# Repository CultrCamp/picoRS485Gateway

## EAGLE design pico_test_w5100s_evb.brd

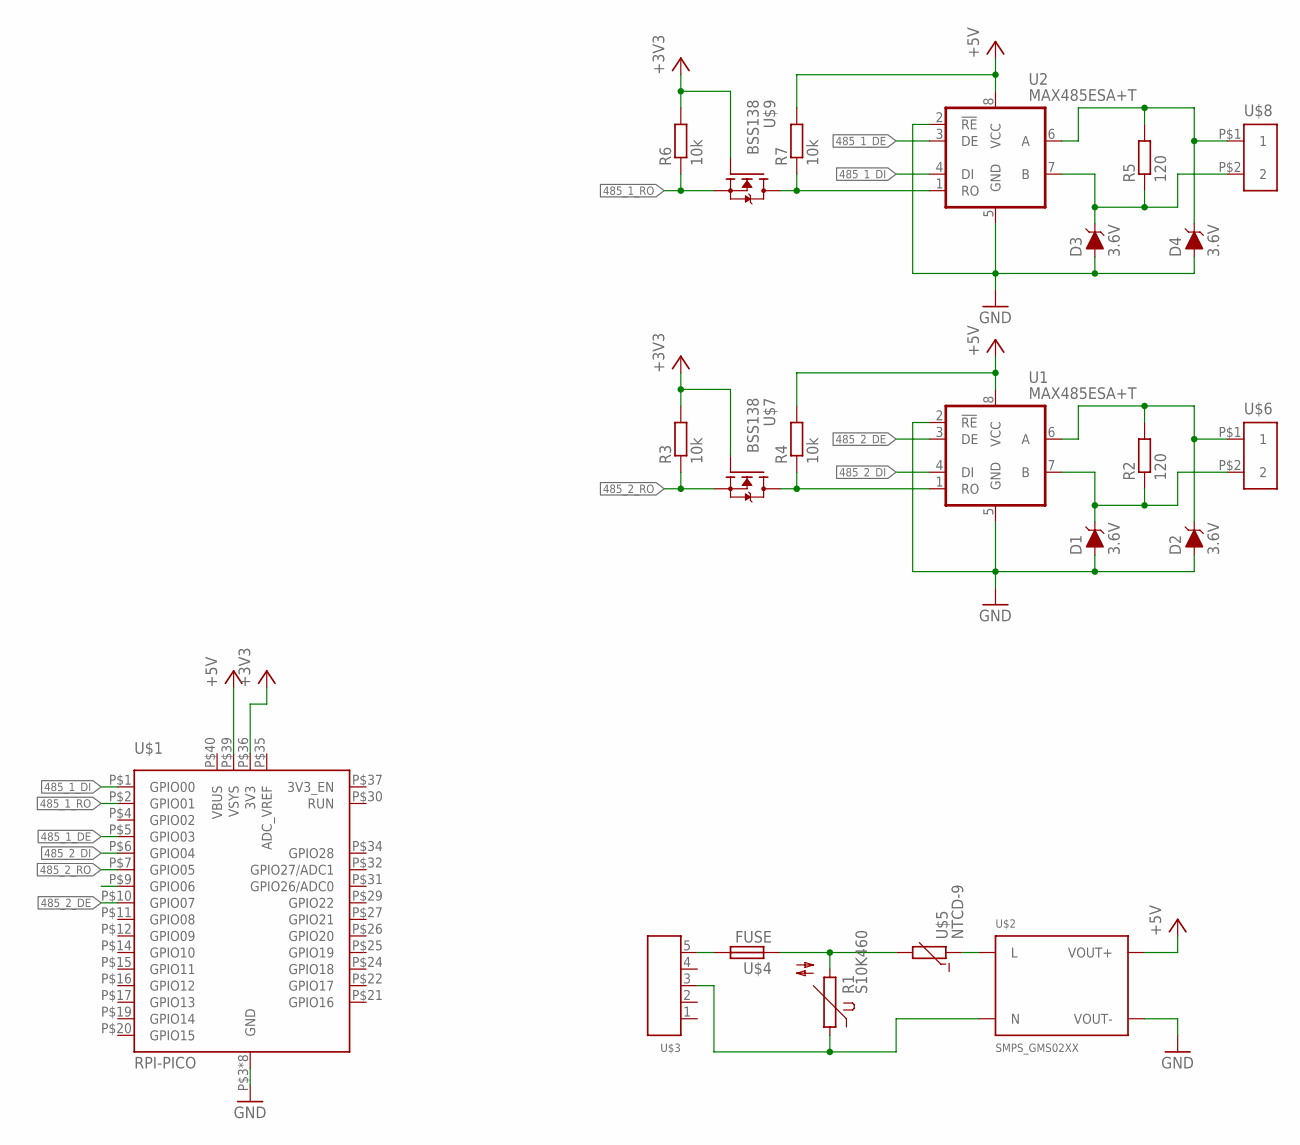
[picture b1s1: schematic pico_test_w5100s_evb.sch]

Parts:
D1, D2, D3, D4: 3.6V; SOD-323
R1: S10K460
R2, R5: 120; R0603
R3, R4, R6, R7: 10k; R0603
U1, U2: MAX485ESA+T; SOIC127P600X175-8N
U$1: RPI-PICO; W5100S-EVB-PICO
U$2: SMPS_GMS02XX; GMS02XX
U$3: XEHDR-5
U$4: FUSE; FUZEX8.5X4.5X5.08
U$5: NTCD-9; NTCXD-9
U$6, U$8: XEHDR-2; 5EHDR-2
U$7, U$9: BSS138; SOT95P240X110-3N

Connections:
485_1_DE: U2.3 (DE), U$1.P$5 (GPIO03)
485_1_DI: U2.4 (DI), U$1.P$1 (GPIO00)
485_1_RO: R6.1, U$1.P$2 (GPIO01), U$9.2 (S)
485_2_DE: U1.3 (DE), U$1.P$10 (GPIO07)
485_2_DI: U1.4 (DI), U$1.P$6 (GPIO04)
485_2_RO: R3.1, U$1.P$7 (GPIO05), U$7.2 (S)
+3V3: R3.2, R6.2, U$1.P$36 (3V3), U$7.1 (G), U$9.1 (G)
+5V: R4.2, R7.2, U1.8 (VCC), U2.8 (VCC), U$1.P$39 (VSYS), U$2.DC+ (VOUT+)
GND: D1.A, D2.A, D3.A, D4.A, U1.2 (!RE), U1.5 (GND), U2.2 (!RE), U2.5 (GND), U$1.P$3 (GND), U$1.P$8 (GND), U$1.P$13 (GND), U$1.P$18 (GND), U$1.P$23 (GND), U$1.P$28 (GND), U$1.P$33 (GND), U$1.P$38 (GND), U$2.DC- (VOUT-)
unnamed: U$3.5, U$4.P$2 (2)
unnamed: R1.2, U$4.P$1 (1), U$5.P$2 (2)
unnamed: U$2.P$1 (L), U$5.P$1 (1)
unnamed: R1.1, U$2.P$2 (N), U$3.3
unnamed: R4.1, U1.1 (RO), U$7.3 (D)
unnamed: D1.C, R2.1, U1.7 (B), U$6.P$2 (2)
unnamed: D2.C, R2.2, U1.6 (A), U$6.P$1 (1)
unnamed: D3.C, R5.1, U2.7 (B), U$8.P$2 (2)
unnamed: D4.C, R5.2, U2.6 (A), U$8.P$1 (1)
unnamed: R7.1, U2.1 (RO), U$9.3 (D)

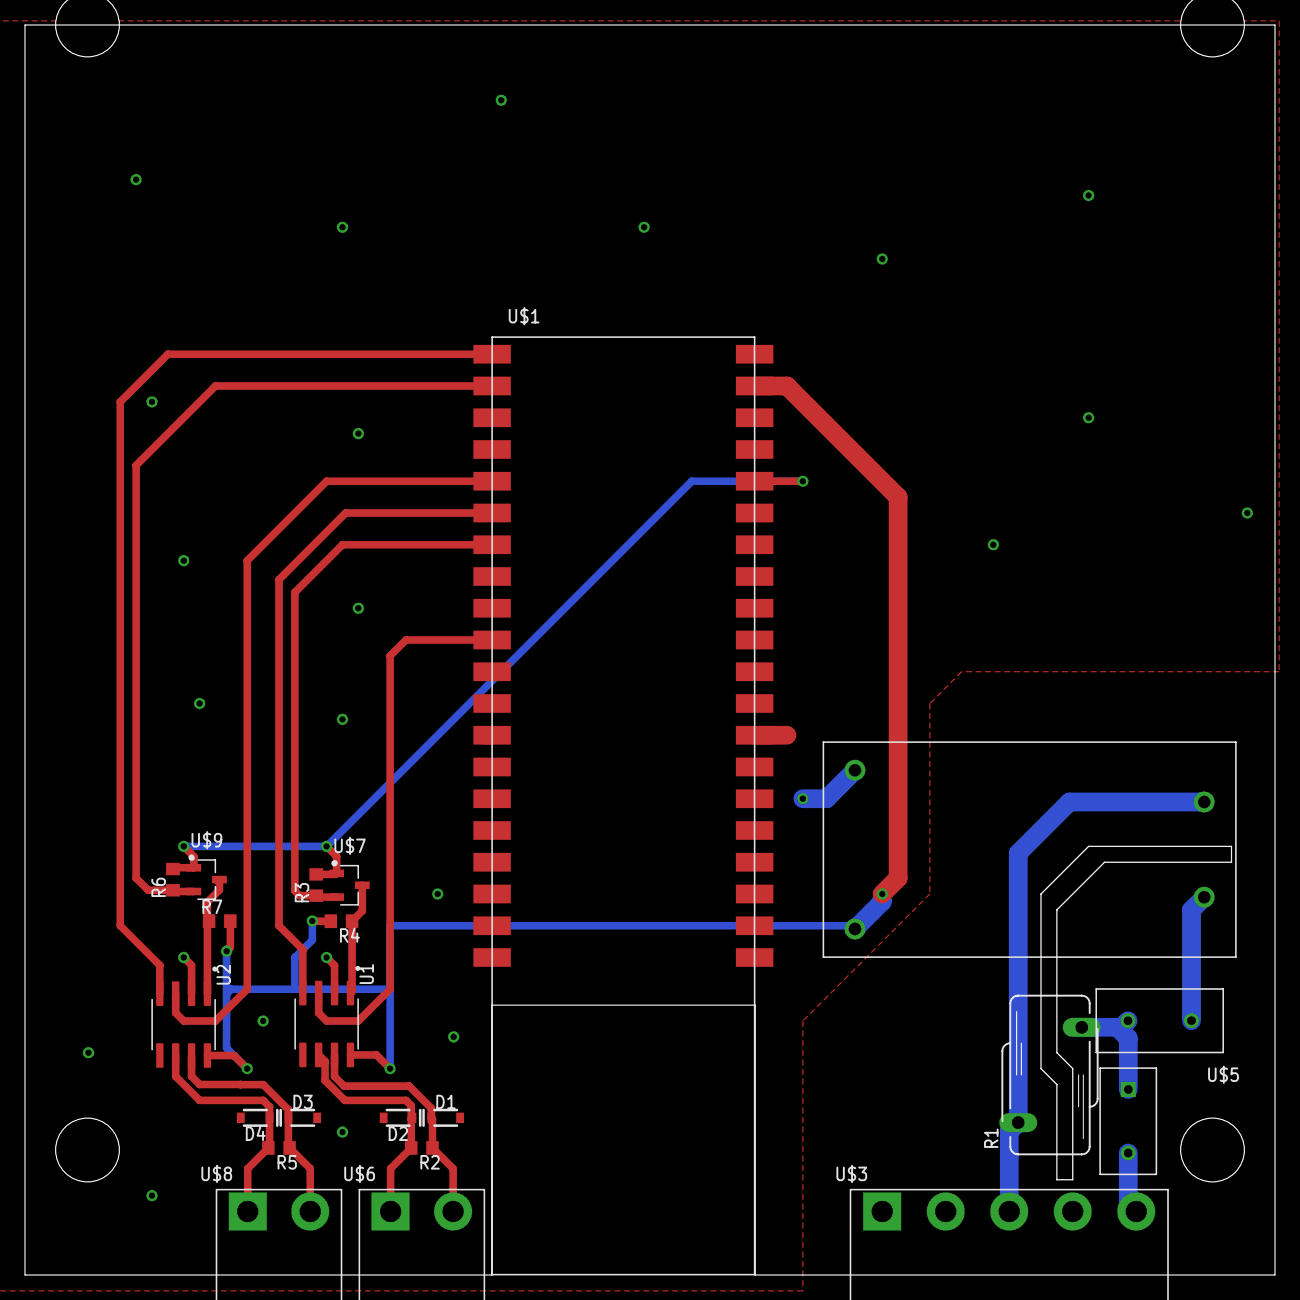
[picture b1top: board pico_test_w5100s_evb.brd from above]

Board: 2 copper layers, 99.9 x 99.9 mm, 22 parts (0 on the bottom side), 19 nets.

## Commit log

2022-08-29 gerber
